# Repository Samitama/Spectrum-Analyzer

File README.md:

# Spectrum-Analyzer
My own spectrum analyzer 
Powered by Raspberry Pi Pico and NRF24L01+

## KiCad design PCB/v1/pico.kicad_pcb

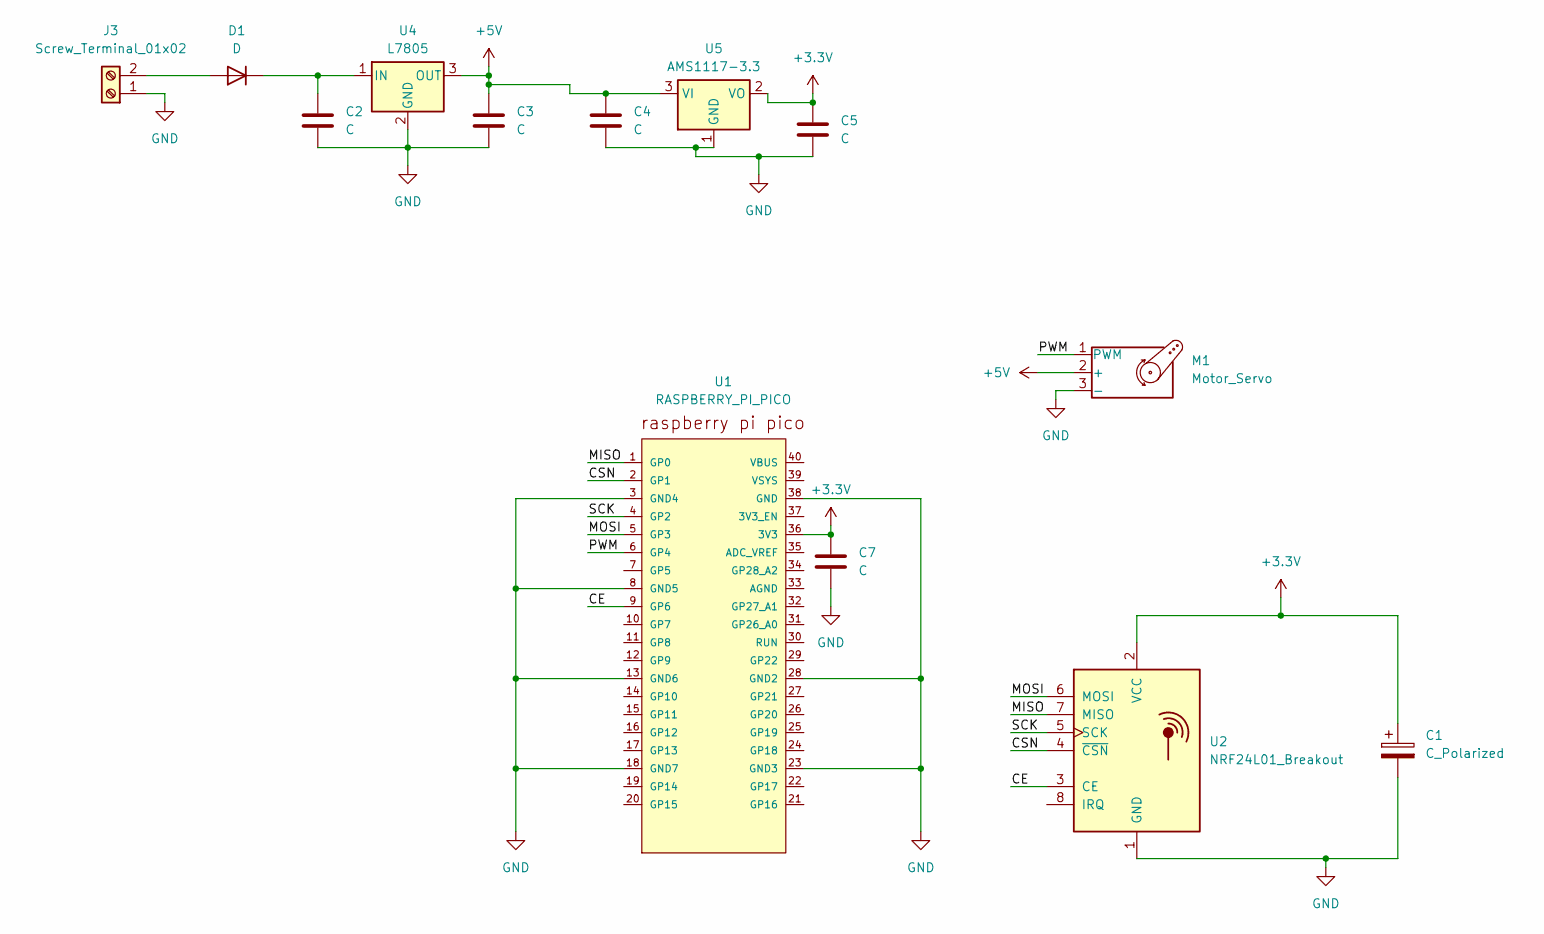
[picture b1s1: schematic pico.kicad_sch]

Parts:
C1: C_Polarized; CP_Radial_D6.3mm_P2.50mm
C2, C3, C4, C5, C7: C; C_1206_3216Metric_Pad1.33x1.80mm_HandSolder
D1: D; D_SMA_Handsoldering
J3: Screw_Terminal_01x02; TerminalBlock_Altech_AK300-2_P5.00mm
M1: Motor_Servo; PinHeader_1x03_P2.54mm_Vertical
U1: RASPBERRY_PI_PICO; RaspberryPi_Pico_Common_THT
U2: NRF24L01_Breakout; nRF24L01_Breakout
U4: L7805; TO-220-3_Vertical
U5: AMS1117-3.3; SOT-223-3_TabPin2

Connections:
+3.3V: C1.1, C5.1, C7.1, U1.36 (3V3), U2.2 (VCC), U5.2 (VO)
+5V: C3.1, C4.1, M1.2 (+), U4.3 (OUT), U5.3 (VI)
/CE: U1.9 (GP6), U2.3 (CE)
/CSN: U1.2 (GP1), U2.4 (~CSN)
/MISO: U1.1 (GP0), U2.7 (MISO)
/MOSI: U1.5 (GP3), U2.6 (MOSI)
/PWM: M1.1 (PWM), U1.6 (GP4)
/SCK: U1.4 (GP2), U2.5 (SCK)
GND: C1.2, C2.2, C3.2, C4.2, C5.2, C7.2, J3.1, M1.3 (-), U1.3 (GND4), U1.8 (GND5), U1.13 (GND6), U1.18 (GND7), U1.23 (GND3), U1.28 (GND2), U1.38 (GND), U2.1 (GND), U4.2 (GND), U5.1 (GND)
unnamed: D1.2 (A), J3.2
unnamed: C2.1, D1.1 (K), U4.1 (IN)

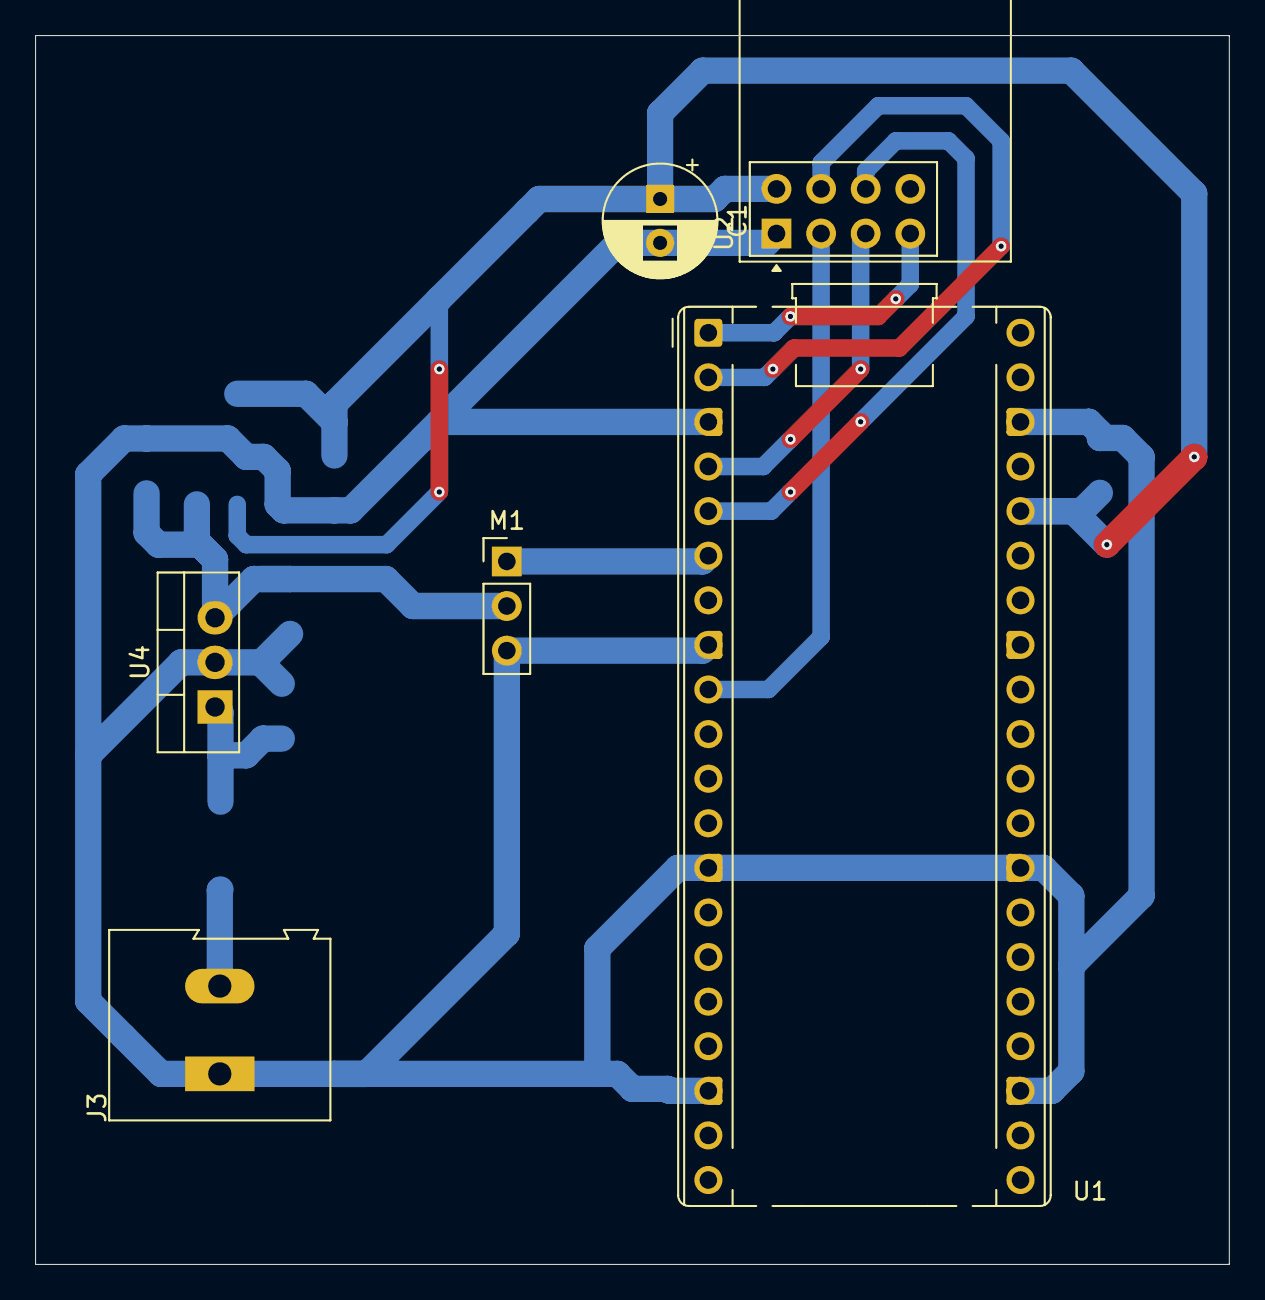
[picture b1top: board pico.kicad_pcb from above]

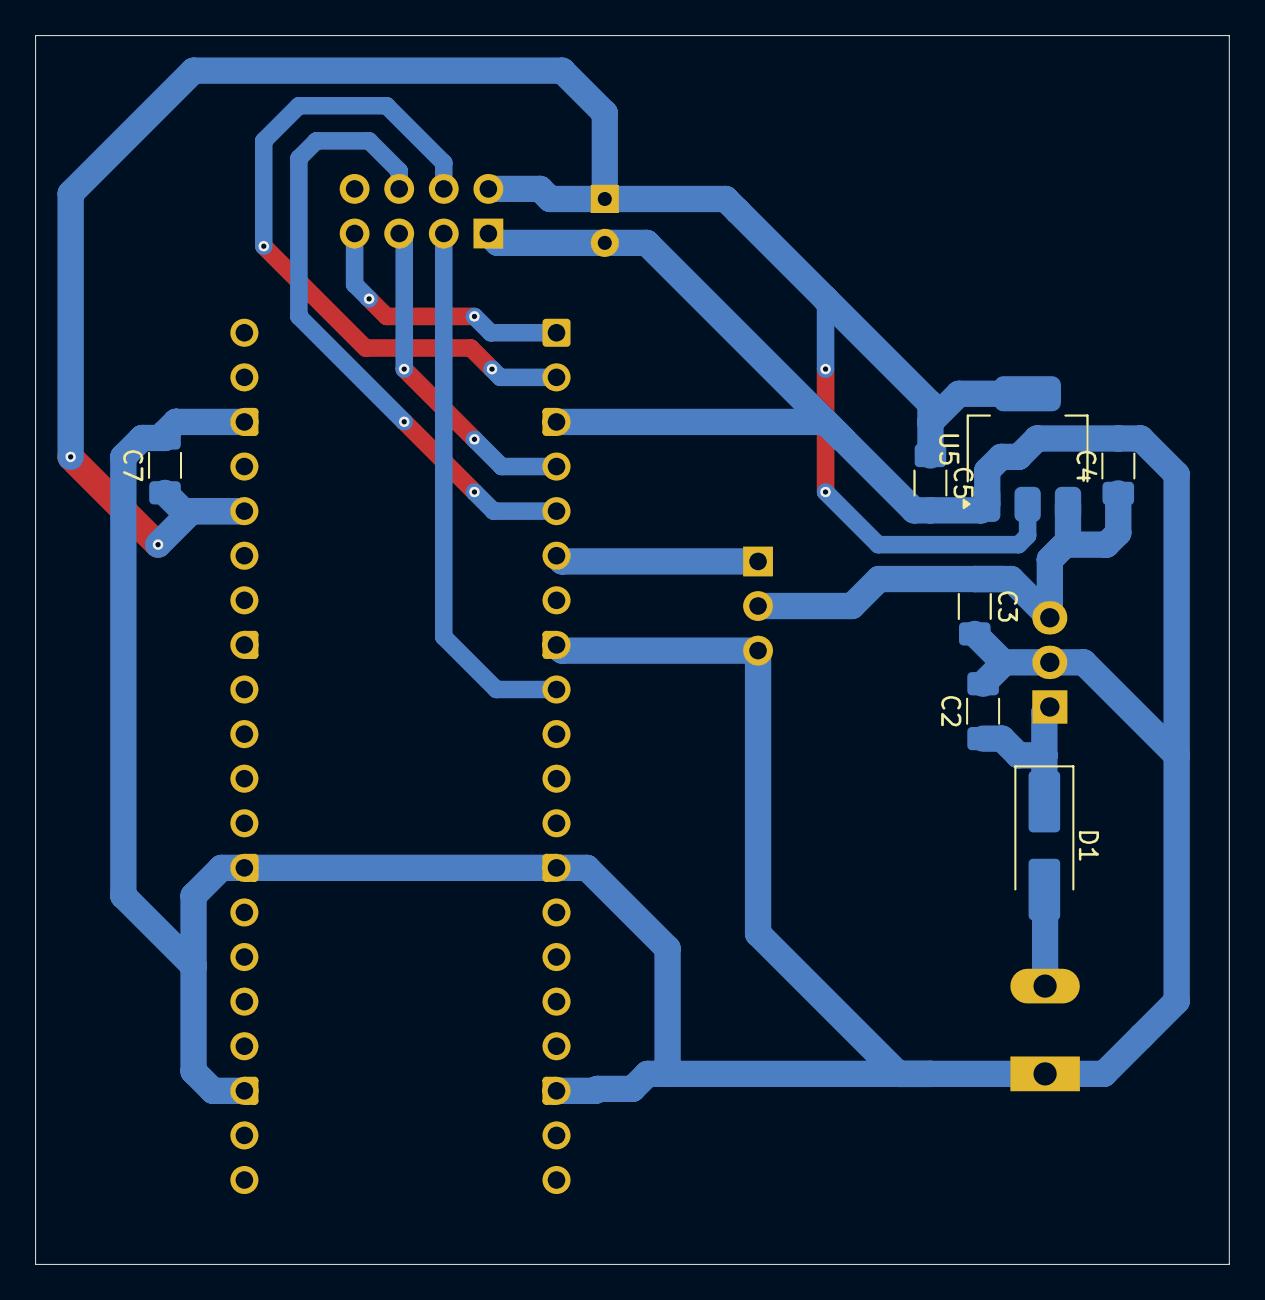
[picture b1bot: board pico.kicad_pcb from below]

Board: 2 copper layers, 68.0 x 70.0 mm, 13 parts (7 on the bottom side), 11 nets.

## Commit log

2025-05-20 Updated gui and python file
    Updated ui and python file uploading
2025-05-20 Updated pico and nrf24l01+ code files
    Uploading pico c++ sdk and nrf24l01 library used
2025-05-20 add .gitignore
2025-05-20 Update a Pico source and Python Gui files
2025-05-21 Adding PCB files on kicad v1
2025-05-21 GUI update
2025-11-08 added to .ui file in python file
2025-11-08 wrong file
